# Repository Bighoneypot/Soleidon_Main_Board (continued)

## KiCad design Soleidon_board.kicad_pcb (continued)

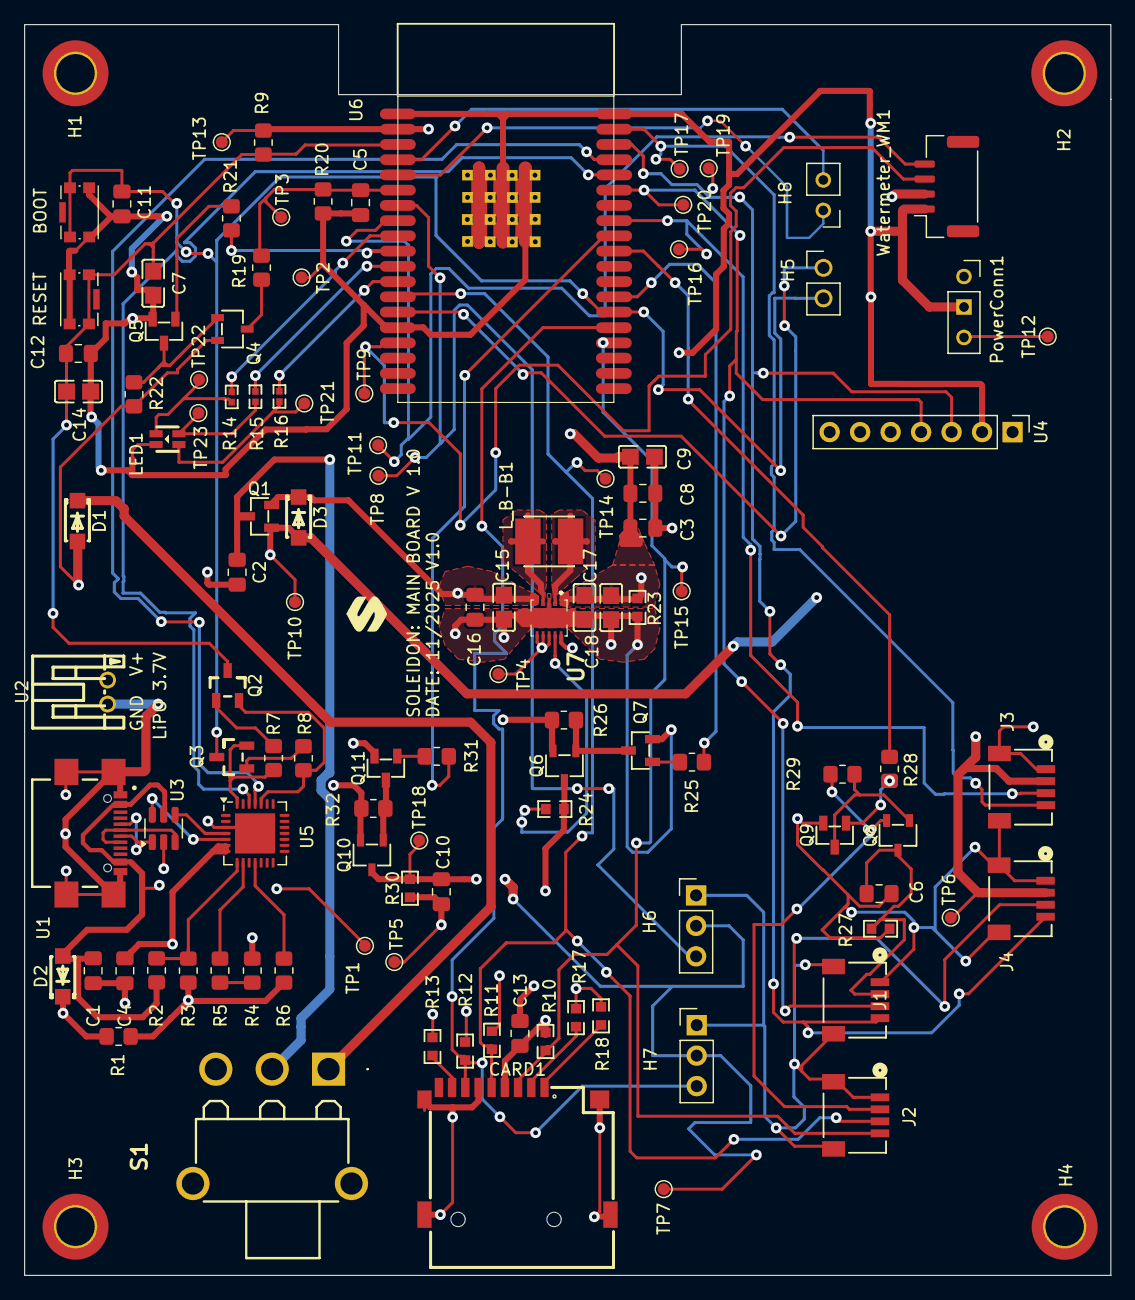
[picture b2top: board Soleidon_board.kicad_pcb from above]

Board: 4 copper layers, 90.5 x 104.2 mm, 114 parts (0 on the bottom side), 65 nets.

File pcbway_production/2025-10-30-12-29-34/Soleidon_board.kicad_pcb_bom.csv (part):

Designator,Quantity,Value,Footprint,Package,MPN,DNP,Mount_Type,REF,Description,Manufacturer Part,Manufacturer,Supplier Part,Supplier,LCSC Part Name,Height,Manufacturer_Name,MF,Description_1,Price,SnapEDA_Link,MP,Availability,Check_prices
"C1, C10, C11, C12, C13, C16, C2, C3, C4, C5, C6, C8",12,104,C_0805_2012Metric_Pad1.18x1.45mm_HandSolder,,,,smt,C49678,,,,,,,,,,,,,,,
C14,1,10uF ±10% 16V,CAP_10uF_CL21A106KOQNNNE,,,,tht,,Capacitance: Tolerance:±10% Tolerance:±10% Voltage Rated: Temperature Coefficient:,CL21A106KOQNNNE,SAMSUNG(三星),C1713,LCSC,10uF ±10% 16V,,,,,,,,,
"C15, C17",2,10uF ±10% 10V,CL10A106KP8NNNC,,,,tht,,Capacitance: Tolerance:±10% Tolerance:±10% Voltage Rated: Temperature Coefficient:,CL10A106KP8NNNC,SAMSUNG(三星),C19702,LCSC,10uF ±10% 10V,,,,,,,,,
C18,1,4.7uF,CL10A475KP8NNNC,,,,tht,,Capacitance: Tolerance:±10% Tolerance:±10% Voltage Rated: Temperature Coefficient:,CL10A475KP8NNNC,SAMSUNG(三星),C1705,LCSC,4.7uF ±10% 10V,,,,,,,,,
C7,1,1uF ±10% 50V,CL10A105KB8NNNC,,,,tht,,Capacitance: Tolerance:±10% Tolerance:±10% Voltage Rated: Temperature Coefficient:,CL10A105KB8NNNC,SAMSUNG(三星),C15849,LCSC,1uF ±10% 50V,,,,,,,,,
C9,1,22uF ±20% 25V,CAP_22uF_CL21A226MAQNNNE,,,,tht,,Capacitance: Tolerance:±20% Tolerance:±20% Voltage Rated: Temperature Coefficient:,CL21A226MAQNNNE,SAMSUNG(三星),C45783,LCSC,22uF ±20% 25V,,,,,,,,,
CARD1,1,micro SD-CARD TF PUSH,TF-SMD_TF-PUSH-micro_SD_card_slot,,,,tht,,Card Connection Mode:Self-bouncing Card Type:MicroSD card (TF card) Connector Type:Card Slot Additional Card Detection Pins:None Supplementary Features:- Maximum Body Height:2mm Operating Temperature Range:-20°C~+90°C Operating Temperature Range:-20°C~+90°C,TF PUSH,SHOU HAN(首韩),C393941,LCSC,自弹式 MicroSD卡(TF卡) 卡座,,,,,,,,,
"D1, D2, D3",3,RB168MM-40TR,RB168MM-40TR,,,,tht,,Diode Configuration:Independent Type Forward Voltage (Vf@If):600mV@1A Reverse Voltage (Vr):40V Rectified Current:1A Reverse Leakage Current (Ir):50nA@40V,RB168MM-40TR,ROHM(罗姆),C509936,LCSC,电压:40V 电流:1A,,,,,,,,,
H5,1,Header-Female-2.54_1x2,PinHeader_1x02_P2.54mm_Vertical,,,Yes,tht,,"Generic screw terminal, single row, 01x02, script generated (kicad-library-utils/schlib/autogen/connector/)",2.54-1*3P母,BOOMELE(博穆精密),C146243,LCSC,间距:2.54mm 直插,,,,,,,,,
H6,1,Header-Female-2.54_1x6,PinHeader_1x03_P2.54mm_Vertical,,,Yes,tht,,"Generic screw terminal, single row, 01x03, script generated (kicad-library-utils/schlib/autogen/connector/)",2.54-1*6P母,BOOMELE(博穆精密),C40877,LCSC,间距:2.54mm 1x6P 直插,,,,,,,,,
H7,1,Header-Female-2.54_1x3,PinHeader_1x03_P2.54mm_Vertical,,,Yes,tht,,Pitch:2.54mm Row Spacing:- Mounting Type:Straight Number of Rows:Plugin Number of Holes:3P Insulation Height:- Contact Material:- Contact Plating:Gold,2.54-1*3P母,BOOMELE(博穆精密),C146243,LCSC,间距:2.54mm 直插,,,,,,,,,
H8,1,Header-Female-2.54_1x2,PinHeader_1x02_P2.54mm_Vertical,,,Yes,tht,,Holes Structure:1x2P Pitch:2.54mm Row Spacing:- Mounting Type:Straight Number of Rows:Plugin Number of Holes:2P Insulation Height:- Contact Material:- Contact Plating:-,2.54-1*2P母,BOOMELE(博穆精密),C49661,LCSC,间距:2.54mm 1x2P 直插,,,,,,,,,
"J1, J2, J3, J4",4,SM04B-SRSS-TB,CONN_SM04B-SRSS-TB_JST,,,,smt,,,,,,,,,,,,,,,,
LED1,1,TJ-S1615CY6TGLCCSRGB-A5,TJ-S1615CY6TGLCCSRGB-A5,,,,tht,,Diode Configuration:Common Cathode Luminous Intensity:G:300mcd~800mcd；B:60mcd~200mcd；R:60mcd~200mcd Viewing Angle:120° Lens Color:Colorless Transparent Lens Installation Method:Positive Stick Operating Temperature:-40°C~+80°C Operating Temperature:-40°C~+80°C,TJ-S1615CY6TGLCCSRGB-A5,TOGIALED(统佳),C601684,LCSC,RGB三色,,,,,,,,,
L_B-B1,1,2.2uH ±20% 3.2A,IND_2.2uH_SWPA4018S2R2MT,,,,tht,,Inductance: Tolerance:±20% Tolerance:±20% Rated Current: Current - Saturation(Isat):3.2A DC Resistance(DCR): Type:- Ratings:-,SWPA4018S2R2MT,Sunlord(顺络),C50543,LCSC,2.2uH ±20% 3.2A,,,,,,,,,
PowerConn1,1,Header-Female-2.54_1x2,PinSocket_1x03_P2.54mm_Vertical,,,,tht,,"Generic screw terminal, single row, 01x03, script generated (kicad-library-utils/schlib/autogen/connector/)",2.54-1*2P母,BOOMELE(博穆精密),C49661,LCSC,间距:2.54mm 1x2P 直插,,,,,,,,,
Q1,1,PMOSFET-DMP1045U-7,PMOSFET-DMP1045U-7,,,,tht,,"Type:1 Piece P-Channel Drain Source Voltage (Vdss): Continuous Drain Current (Id): Drain Source On Resistance (RDS(on)@Vgs,Id):31mΩ@4.5V,4A Power Dissipation (Pd): Gate Threshold Voltage (Vgs(th)@Id):1V@250uA Total Gate Charge (Qg@Vgs):15.8nC@4.5V Input C",DMP1045U-7,DIODES(美台),C177033,LCSC,1个P沟道 耐压:12V 电流:4A,,,,,,,,,
"Q10, Q4, Q6, Q8",4,P-MOSFET-ENH-BSS84LT1G,BSS84LT1G,,,,tht,,"Type:1个PChannel Drain Source Voltage (Vdss): Continuous Drain Current (Id): Power Dissipation (Pd): Drain Source On Resistance (RDS(on)@Vgs,Id):10Ω@5V,100mA Gate Threshold Voltage (Vgs(th)@Id):2V@250uA Input Capacitance (Ciss@Vds):30pF@5V Operating Temper",BSS84LT1G,onsemi(安森美),C82079,LCSC,1个P沟道 耐压:50V 电流:130mA,,,,,,,,,
"Q11, Q5, Q7, Q9",4,N-MOSFET-ENH-2N7002,2N7002,,,,tht,,"Type:1 N-Channel Drain Source Voltage (Vdss): Continuous Drain Current (Id): Drain Source On Resistance (RDS(on)@Vgs,Id):5Ω@10V Power Dissipation (Pd):225mW Gate Threshold Voltage (Vgs(th)@Id):2.5V@250uA Input Capacitance (Ciss@Vds):50pF Reverse Transfer",2N7002,CJ(江苏长电/长晶),C8545,LCSC,1个N沟道 耐压:60V 电流:115mA,,,,,,,,,
"Q2, Q3",2,2N3904S-RTK/PS,2n3904S-RTKPS,,,,tht,,"type:NPN Current - Collector(Ic): Collector - Emitter Voltage VCEO:40V Pd - Power Dissipation:350mW DC Current Gain:100@10mA,1V DC Current Gain:100@10mA,1V Transition frequency(fT):300MHz Current - Collector Cutoff:- Vce Saturation(VCE(sat)):300mV Operati",2N3904S-RTK/PS,KEC,C18536,LCSC,2N3904S-RTK/PS,,,,,,,,,
"R1, R19, R20, R22, R26, R29, R32, R6, R7, R8, R9",11,10K,R_0805_2012Metric_Pad1.20x1.40mm_HandSolder,,,,smt,C17414,,,,,,,,,,,,,,,
"R10, R11, R12, R13, R17, R18",6,7.5kΩ,0603WAF7501T5E,,,,tht,,Type:Thick Film Resistors Resistance:7.5kΩ Tolerance:±1% Tolerance:±1% Power(Watts): Overload Voltage (Max): Temperature Coefficient:±100ppm/°C Temperature Coefficient:±100ppm/°C Operating Temperature Range:-55°C~+155°C Operating Temperature Range:-55°C~+155°C,0603WAF7501T5E,UNI-ROYAL(厚声),C23234,LCSC,7.5kΩ ±1% 100mW,,,,,,,,,
R14,1,150Ω ±1% 62.5mW,RES_10K_0402WGF1002TCE,,,,tht,,62.5mW Thick Film Resistors 50V ±100ppm/℃ ±1% 150Ω 0402 Chip Resistor - Surface,RC0402FR-07150RL,YAGEO ,C138054,,150Ω ±1% 62.5mW,,,,,,,,,
"R15, R16",2,36Ω ±1% 62.5mW,RES_10K_0402WGF1002TCE,,,,tht,,62.5mW Thick Film Resistors 50V ±100ppm/℃ ±5% 36Ω 0402 Chip Resistor - Surface Mount ROHS,FRC0402J360 TS,FOJAN,C2906935,,36Ω ±1% 62.5mW,,,,,,,,,
R2,1,22K1,R_0805_2012Metric_Pad1.20x1.40mm_HandSolder,,,,smt,C2930182,,,,,,,,,,,,,,,
"R21, R25, R28, R31",4,100,R_0805_2012Metric_Pad1.20x1.40mm_HandSolder,,,,smt,C17408,,,,,,,,,,,,,,,
R23,1,220Ω,0603WAJ0221T5E,,,,tht,C1226,Type:Thick Film Resistors Resistance: Tolerance:±5% Tolerance:±5% Power(Watts): Overload Voltage (Max): Temperature Coefficient:±100ppm/°C Temperature Coefficient:±100ppm/°C Operating Temperature Range:-55°C~+155°C Operating Temperature Range:-55°C~+155°C,0603WAJ0221T5E,UNI-ROYAL(厚声),C1226,LCSC,220Ω ±5% 100mW,,,,,,,,,
"R24, R27, R30",3,4.7kΩ ±1% 100mW,0603WAF4701T5E,,,,tht,,Type:Thick Film Resistors Resistance:4.7kΩ Tolerance:±1% Tolerance:±1% Power(Watts): Overload Voltage (Max): Temperature Coefficient:±100ppm/°C Temperature Coefficient:±100ppm/°C Operating Temperature Range:-55°C~+155°C Operating Temperature Range:-55°C~+155°C,0603WAF4701T5E,UNI-ROYAL(厚声),C23162,LCSC,4.7kΩ ±1% 100mW,,,,,,,,,
R3,1,47K5,R_0805_2012Metric_Pad1.20x1.40mm_HandSolder,,,,smt,C245335,,,,,,,,,,,,,,,
"R4, R5",2,1K,R_0805_2012Metric_Pad1.20x1.40mm_HandSolder,,,,smt,C17513,,,,,,,,,,,,,,,
S1,1,MFP126DRA-UL,MFP126DRAUL,,MFP126DRA-UL,,tht,,"Slide Switch, 1 Positions, On-on, Horizontal, 5A, 28VDC, 5 PCB Hole Cnt, Solder Terminal, Through Hole-right Angle",,,,,,6.85,KNITTER-SWITCH,,,,,,,
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
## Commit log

2025-11-03 Repository first upload after production
2025-11-07 add cape project
